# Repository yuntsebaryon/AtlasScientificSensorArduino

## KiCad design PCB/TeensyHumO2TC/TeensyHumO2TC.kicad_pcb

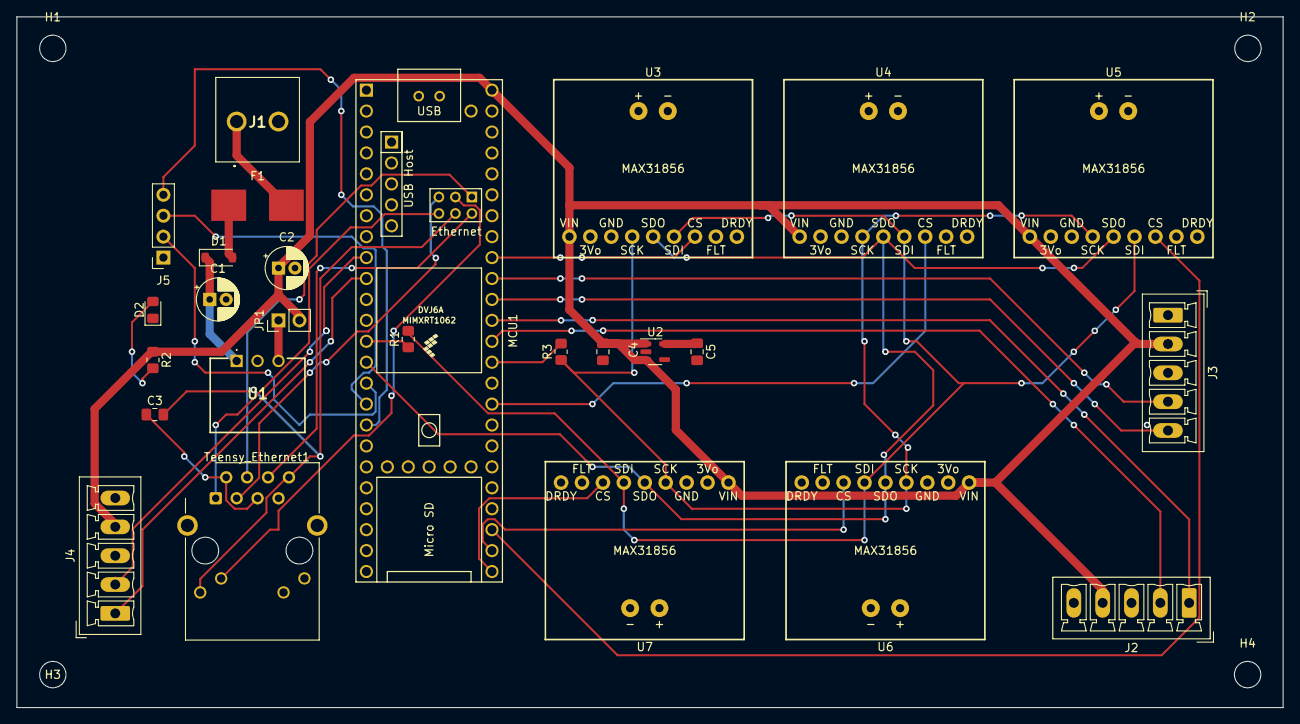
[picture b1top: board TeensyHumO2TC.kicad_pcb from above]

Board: 2 copper layers, 153.7 x 83.8 mm, 30 parts (0 on the bottom side), 28 nets.

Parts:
C1: 10u; CP_Radial_D5.0mm_P2.00mm
C2: 22u; CP_Radial_D5.0mm_P2.00mm
C3: 100n; C_0805_2012Metric_Pad1.18x1.45mm_HandSolder
C4, C5: 1u; C_0805_2012Metric_Pad1.18x1.45mm_HandSolder
D1: D; D_SOD-123
D2: LED 5VOK; LED_0805_2012Metric_Pad1.15x1.40mm_HandSolder
F1: 1A; smd_fuse
H1, H2, H3, H4: MountingHole; MountingHole_3.2mm_M3_DIN965
J1: Screw_Terminal_01x02; TB00750802BE
J2, J3, J4: Conn_01x05_Socket; PhoenixContact_MCV_1,5_5-G-3.5_1x05_P3.50mm_Vertical
J5: OLED Display I2C; PinSocket_1x04_P2.54mm_Vertical
JP1: PS; PinHeader_1x02_P2.54mm_Vertical
MCU1: Teensy41
R1, R3: 22R; R_0805_2012Metric_Pad1.20x1.40mm_HandSolder
R2: 1.5k; R_0805_2012Metric_Pad1.20x1.40mm_HandSolder
Teensy_Ethernet1: RJ45_Cetus_J1B1211CCD_Horizontal
U1: N7805; N78051C
U2: NCP163ASN330T1G; SOT-23-5
U3, U4, U5, U6, U7: thermo_max31856; MAX31856

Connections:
+3.3VA: C5.1, U2.5 (VOUT)
+5V: C2.1, C4.1, J2.4, J3.2, J4.4, JP1.2 (B), MCU1.48 (VIN), R2.1, U2.1 (VIN), U2.3 (EN), U3.1 (VIN), U4.1 (VIN), U5.1 (VIN), U6.1 (VIN), U7.1 (VIN)
/CLK: R3.1, U3.4 (SCK), U4.4 (SCK), U5.4 (SCK), U6.4 (SCK), U7.4 (SCK)
/CS_1: MCU1.40 (18_A4_SDA), U3.7 (CS)
/CS_2: MCU1.33 (41_A17), U4.7 (CS)
/CS_3: MCU1.27 (35_TX8), U5.7 (CS)
/CS_4: MCU1.26 (34_RX8), U6.7 (CS)
/CS_5: MCU1.25 (33_MCLK2), U7.7 (CS)
/SDI: R1.2, U3.6 (SDI), U4.6 (SDI), U5.6 (SDI), U6.6 (SDI), U7.6 (SDI)
/SDO: MCU1.14 (12_MISO_MQSL), U3.5 (SDO), U4.5 (SDO), U5.5 (SDO), U6.5 (SDO), U7.5 (SDO)
GND: C1.2, C2.2, C4.2, C5.2, D2.1 (K), J1.2, J2.3, J2.5, J3.1, J3.3, J4.3, J4.5, J5.1, MCU1.47 (GND), U1.2 (GND/-Vout), U2.2 (GND), U3.3 (GND), U4.3 (GND), U5.3 (GND), U6.3 (GND), U7.3 (GND)
I2C_SCL: J5.3, MCU1.16 (24_A10_TX6_SCL2)
I2C_SDA: J5.4, MCU1.17 (25_A11_RX6_SDA2)
unnamed: C3.1, Teensy_Ethernet1.2, Teensy_Ethernet1.5
unnamed: C3.2, MCU1.64 (GND), Teensy_Ethernet1.8, Teensy_Ethernet1.9
unnamed: D1.2 (A), F1.1
unnamed: C1.1, D1.1 (K), U1.1 (IN)
unnamed: D2.2 (A), R2.2
unnamed: F1.2, J1.1
unnamed: J5.2, MCU1.15 (3V3)
unnamed: JP1.1 (A), U1.3 (+Vout/GND)
unnamed: MCU1.13 (11_MOSI_CTX1), R1.1
unnamed: MCU1.35 (13_SCK_LED), R3.2
unnamed: MCU1.61 (LED), Teensy_Ethernet1.10
unnamed: MCU1.60 (R+), Teensy_Ethernet1.4
unnamed: MCU1.65 (R-), Teensy_Ethernet1.6
unnamed: MCU1.63 (T+), Teensy_Ethernet1.1
unnamed: MCU1.62 (T-), Teensy_Ethernet1.3

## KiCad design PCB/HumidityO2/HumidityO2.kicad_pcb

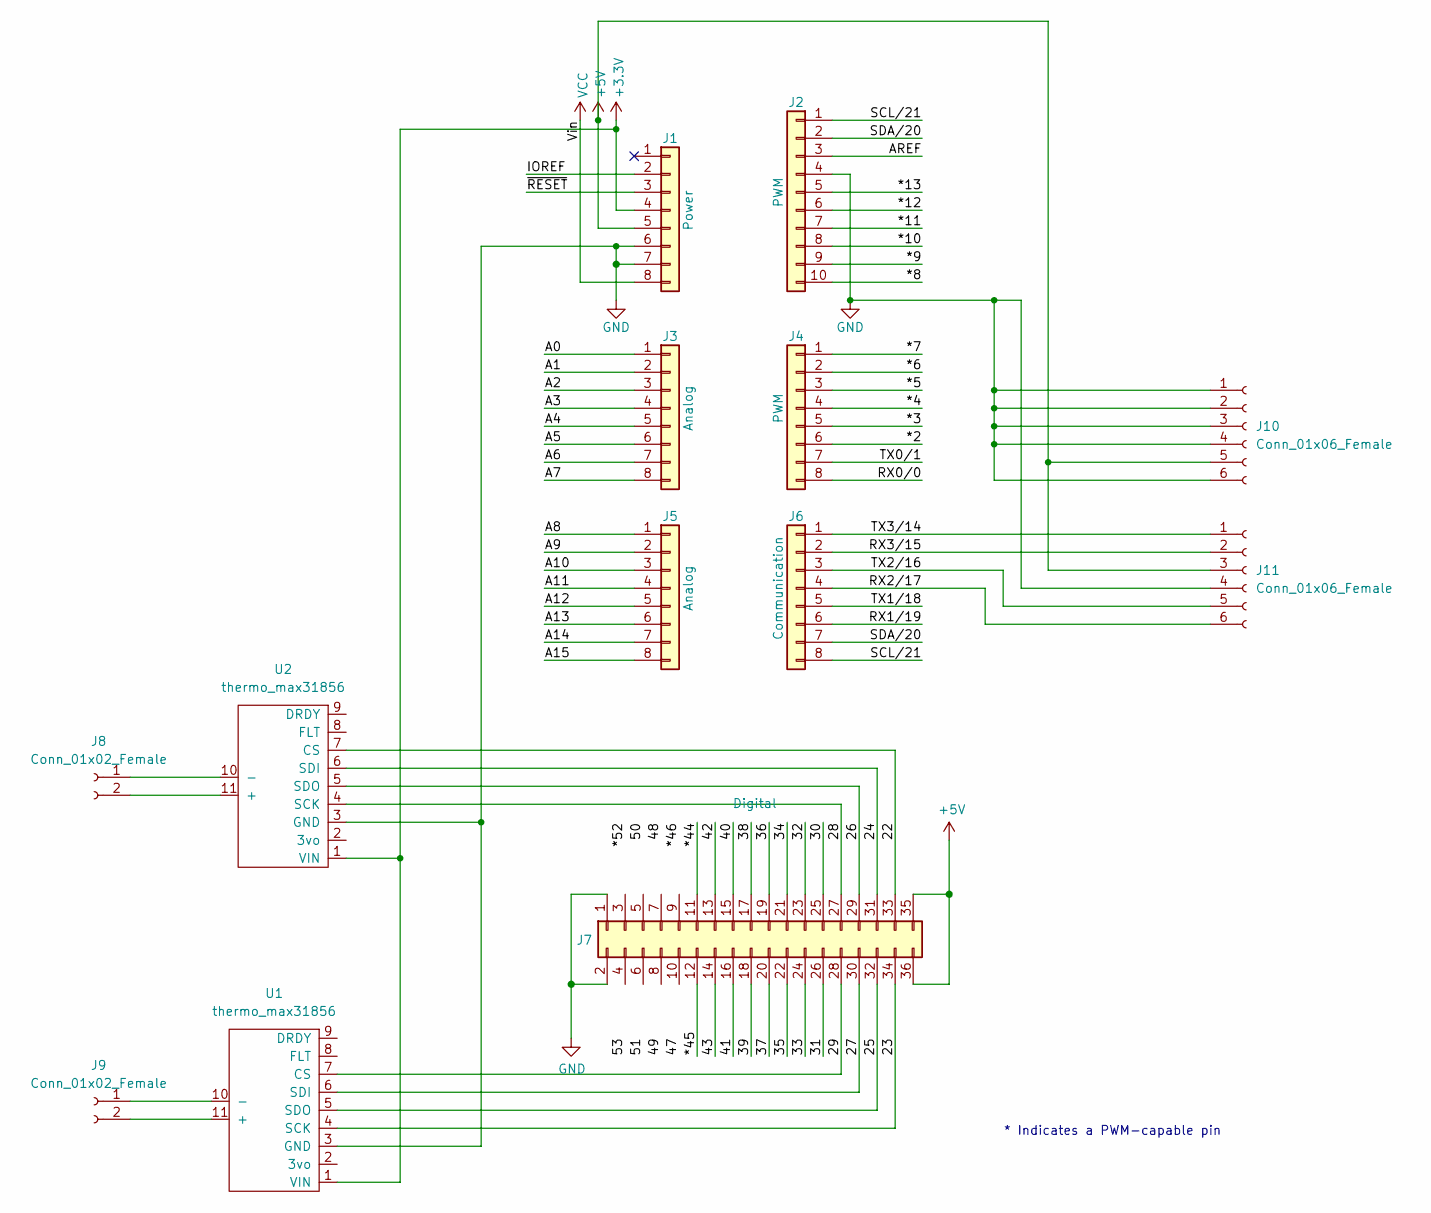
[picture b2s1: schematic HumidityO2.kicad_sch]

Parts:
J1: Power; PinSocket_1x08_P2.54mm_Vertical
J2: PWM; PinSocket_1x10_P2.54mm_Vertical
J3, J5: Analog; PinSocket_1x08_P2.54mm_Vertical
J4: PWM; PinSocket_1x08_P2.54mm_Vertical
J6: Communication; PinSocket_1x08_P2.54mm_Vertical
J7: Digital; PinSocket_2x18_P2.54mm_Vertical
J8, J9: Conn_01x02_Female; PhoenixContact_MCV_1,5_2-G-3.5_1x02_P3.50mm_Vertical
J10, J11: Conn_01x06_Female; PhoenixContact_MCV_1,5_6-G-3.5_1x06_P3.50mm_Vertical
U1, U2: thermo_max31856; MAX31856

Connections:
+3V3: J1.4, U1.1 (VIN), U2.1 (VIN)
+5V: J1.5, J7.35, J7.36, J10.5, J11.3
/22: J7.33, U2.7 (CS)
/23: J7.34, U1.4 (SCK)
/24: J7.31, U2.6 (SDI)
/25: J7.32, U1.5 (SDO)
/26: J7.29, U2.5 (SDO)
/27: J7.30, U1.6 (SDI)
/28: J7.27, U2.4 (SCK)
/29: J7.28, U1.7 (CS)
/30: J7.25
/31: J7.26
/32: J7.23
/33: J7.24
/34: J7.21
/35: J7.22
/36: J7.19
/37: J7.20
/38: J7.17
/39: J7.18
/40: J7.15
/41: J7.16
/42: J7.13
/43: J7.14
/*2: J4.6
/*3: J4.5
/*4: J4.4
/*5: J4.3
/*6: J4.2
/*7: J4.1
/*8: J2.10
/*9: J2.9
/*10: J2.8
/*11: J2.7
/*12: J2.6
/*13: J2.5
/*44: J7.11
/*45: J7.12
/A0: J3.1
/A1: J3.2
/A2: J3.3
/A3: J3.4
/A4: J3.5
/A5: J3.6
/A6: J3.7
/A7: J3.8
/A8: J5.1
/A9: J5.2
/A10: J5.3
/A11: J5.4
/A12: J5.5
/A13: J5.6
/A14: J5.7
/A15: J5.8
/AREF: J2.3
/IOREF: J1.2
/RX0/0: J4.8
/RX1/19: J6.6
/RX2/17: J6.4, J11.6
/RX3/15: J6.2, J11.2
/SCL/21: J2.1, J6.8
/SDA/20: J2.2, J6.7
/TX0/1: J4.7
/TX1/18: J6.5
/TX2/16: J6.3, J11.5
/TX3/14: J6.1, J11.1
/~RESET: J1.3
GND: J1.6, J1.7, J2.4, J7.1, J7.2, J10.1, J10.2, J10.3, J10.4, J10.6, J11.4, U1.3 (GND), U2.3 (GND)
unnamed: J8.1, U2.10 (-)
unnamed: J8.2, U2.11 (+)
unnamed: J9.1, U1.10 (-)
unnamed: J9.2, U1.11 (+)
VCC: J1.8

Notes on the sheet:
* Indicates a PWM-capable pin

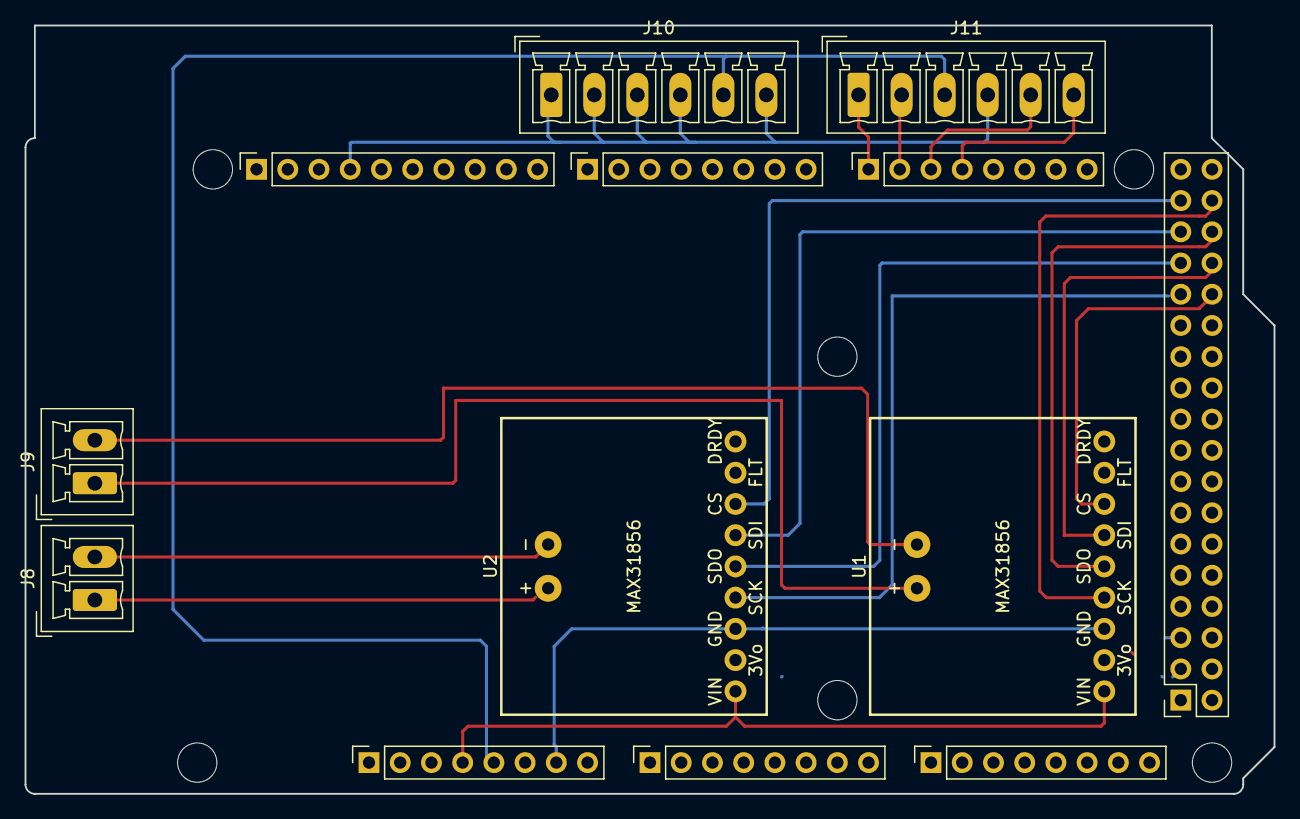
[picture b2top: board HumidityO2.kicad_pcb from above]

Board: 2 copper layers, 101.6 x 62.5 mm, 19 parts (0 on the bottom side), 21 nets.

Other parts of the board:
MH1, MH2, MH3, MH4, MH5, MH6: MountingHole_3.2mm

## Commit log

2022-08-07 the O2 has the original sample code, while the humidity I added a couple of lines for the input string
2022-08-11 add arduino mega for humidity sensors, reoragnize the directories
2022-08-11 adjusted the Modbus code, and add the Modbus code to the O2 readout
2022-08-24 read both the humidity and O2 sensors
2022-08-24 add sample code and modbus code
2022-08-24 added comments
2022-08-26 uncomment the modbus code and test it
2023-05-06 add .gitignore
2023-05-11 new pins, add PCB drawing
2023-08-03 new code for teensy
2023-08-03 remove old things
2023-08-03 include *.zip in .gitignore
2023-08-21 new code to measure the humidity, oxygen, temperature, and display the value. also it sends the information via the serial port and daq/teensy_daq.py creates a csv file for the data
2023-08-21 complete the doc and slightly adjust the order of serial prints in the code
2023-09-07 clean up
2023-10-03 fix the dynamic range issue, also use int16_t instead of uint16_t
